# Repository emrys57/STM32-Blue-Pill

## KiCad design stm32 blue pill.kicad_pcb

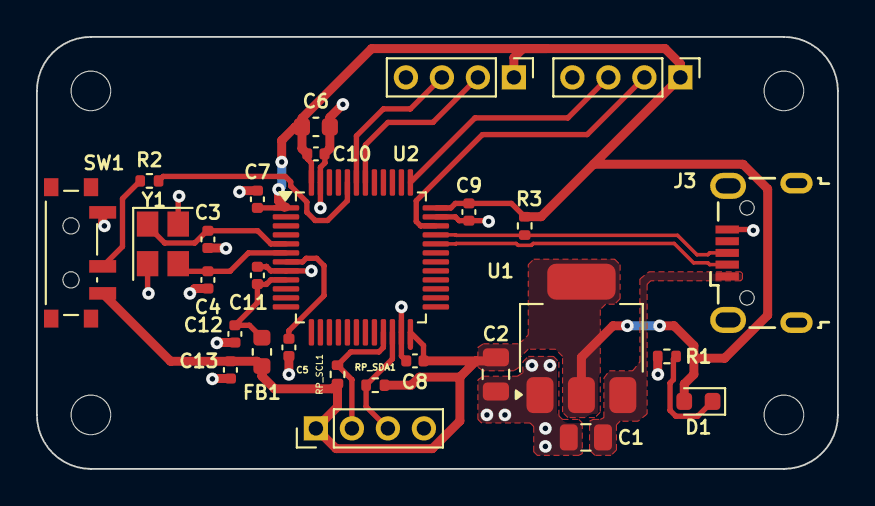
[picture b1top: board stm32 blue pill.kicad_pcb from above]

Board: 2 copper layers, 44.5 x 24.0 mm, 32 parts (0 on the bottom side), 18 nets.

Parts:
C1, C2: 22u; C_0805_2012Metric
C3, C4: 10p; C_0402_1005Metric
C5, C7, C8, C9, C10: 100n; C_0402_1005Metric
C6: 10u; C_0603_1608Metric
C11: 10n; C_0402_1005Metric
C12, C13: 1u; C_0402_1005Metric
D1: GREEN; LED_0603_1608Metric
FB1: 120R; L_0603_1608Metric
H1, H2, H3, H4: MountingHole; MountingHole_2.2mm_M2
J1, J2, J4: Conn_01x04_Male; PinHeader_1x04_P2.00mm_Vertical
J3: USB_B_Micro; USB_Micro-B_Wuerth_629105150521
R1, R3: 1k5; R_0402_1005Metric
R2: 10k; R_0402_1005Metric
RP_SCL1: 2k2; R_0402_1005Metric
RP_SDA1: 2k2; R_0402_1005Metric
SW1: SW_SPDT; SW_SPDT_PCM12
U1: AMS1117-3.3; SOT-223-3_TabPin2
U2: STM32F103C8T6; LQFP-48_7x7mm_P0.5mm
Y1: 16MHz; Crystal_SMD_3225-4Pin_3.2x2.5mm

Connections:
+3.3V: C2.1, C6.1, C7.1, C8.1, C9.1, C10.1, C13.1, D1.2 (A), FB1.2, J1.1, J2.1, J4.1, R3.1, RP_SCL1.1, RP_SDA1.2, SW1.3 (C), U1.2 (VO), U2.1 (VBAT), U2.24 (VDD), U2.36 (VDD), U2.48 (VDD)
+3.3VA: C11.1, C12.1, FB1.1, U2.9 (VDDA)
/BOOT0: R2.2, U2.44 (BOOT0)
/HSE_IN: C3.1, U2.5 (PD0), Y1.1
/HSE_OUT: C4.1, U2.6 (PD1), Y1.3
/I2C2_SCL: J2.2, RP_SCL1.2, U2.21 (PB10)
/I2C2_SDA: J2.3, RP_SDA1.1, U2.22 (PB11)
/NRST: C5.1, U2.7 (NRST)
/PWR_LED_K: D1.1 (K), R1.1
/SWCLK: J4.3, U2.37 (PA14)
/SWDIO: J4.2, U2.34 (PA13)
/SW_BOOT0: R2.1, SW1.2 (B)
/USART1_RX: J1.3, U2.43 (PB7)
/USART1_TX: J1.2, U2.42 (PB6)
/USB_D+: J3.3 (D+), R3.2, U2.33 (PA12)
/USB_D-: J3.2 (D-), U2.32 (PA11)
GND: C1.2, C2.2, C3.2, C4.2, C5.2, C6.2, C7.2, C8.2, C9.2, C10.2, C11.2, C12.2, C13.2, J1.4, J2.4, J3.5 (GND), J4.4, R1.2, SW1.1 (A), U1.1 (GND), U2.8 (VSSA), U2.23 (VSS), U2.35 (VSS), U2.47 (VSS), Y1.2, Y1.4
VBUS: C1.1, J3.1 (VBUS), U1.3 (VI)

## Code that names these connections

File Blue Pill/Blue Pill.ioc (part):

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Mcu.Name=STM32F103C(8-B)Tx
Mcu.Package=LQFP48
Mcu.UserName=STM32F103C8Tx
PA11.Mode=Device
PA11.Signal=USB_DM
PA12.Mode=Device
PA12.Signal=USB_DP
PA13.Mode=Serial_Wire
PA13.Signal=SYS_JTMS-SWDIO
PA14.Mode=Serial_Wire
PA14.Signal=SYS_JTCK-SWCLK
PD0-OSC_IN.Mode=HSE-External-Oscillator
PD0-OSC_IN.Signal=RCC_OSC_IN
PD1-OSC_OUT.Mode=HSE-External-Oscillator
PD1-OSC_OUT.Signal=RCC_OSC_OUT
RCC.HSE_VALUE=16000000
RCC.SYSCLKFreq_VALUE=16000000
RCC.SYSCLKSource=RCC_SYSCLKSOURCE_HSE
board=custom

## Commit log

2022-09-09 Power & Oscillator
    Power & Oscillator Connections.
    Initialized STM32CubeIDE Project
2022-09-11 Power and USB
    Power and USB
2022-09-13 upload
    upload
2024-07-05 schematic updates & pcb init
2024-07-18 layout rough draft
2024-07-18 untested final route draft
2024-07-19 final rough draft
2024-07-20 fixed sch error
2024-10-22 tidying away
